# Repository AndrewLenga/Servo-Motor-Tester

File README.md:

# Servo-Motor-Tester
This repository contains the full design suite—including Schematic, PCB Layout, and 3D CAD models—for a high-stability Servo Motor Tester. Engineered using a modified astable multivibrator topology, this device provides a robust hardware solution for validating RC servo response without the need for a microcontroller.
1. Executive Summary
Standard RC servos operate on a specific Pulse Width Modulation (PWM) protocol, requiring a carrier frequency (period) with a high-state duration.
This design leverages the NE555P precision timer to synthesize this waveform by decoupling the charge and discharge timing constants, ensuring high-fidelity signal reproduction for professional benchtop testing.
3. Circuit Architecture & Signal Integrity
A. Non-Symmetric Astable Topology
In a textbook 555 astable configuration, the duty cycle is constrained to achieve the duty cycle required for servo control, this design incorporates a signal diode in parallel with the discharge path.
Charging Phase: The timing capacitor charges through the series combination of the potentiometer 

Discharging Phase: 
It provides a low-impedance return path to Pin 7 (Discharge), effectively bypassing the primary timing resistors.

Implementation Specifications
Parameter	Specification
Logic Family	Bipolar NE555 / CMOS Equivalent
Input Voltage ( DC (Regulated)
Operating Frequency	
(Targeted for standard RC protocols)
Output Pulse Range  (Min) to  (Max)
Connector Interface	3-Pin Header (Signal-VCC-GND)
4. Documentation & Manufacturing
This project includes a comprehensive set of production files:
Schematic: Hierarchical design focusing on signal flow and net-clearance.

PCB Layout: Optimized for a compact footprint with enhanced ground planes for EMI reduction.

3D Model: STEP/STL files for mechanical integration and enclosure design.

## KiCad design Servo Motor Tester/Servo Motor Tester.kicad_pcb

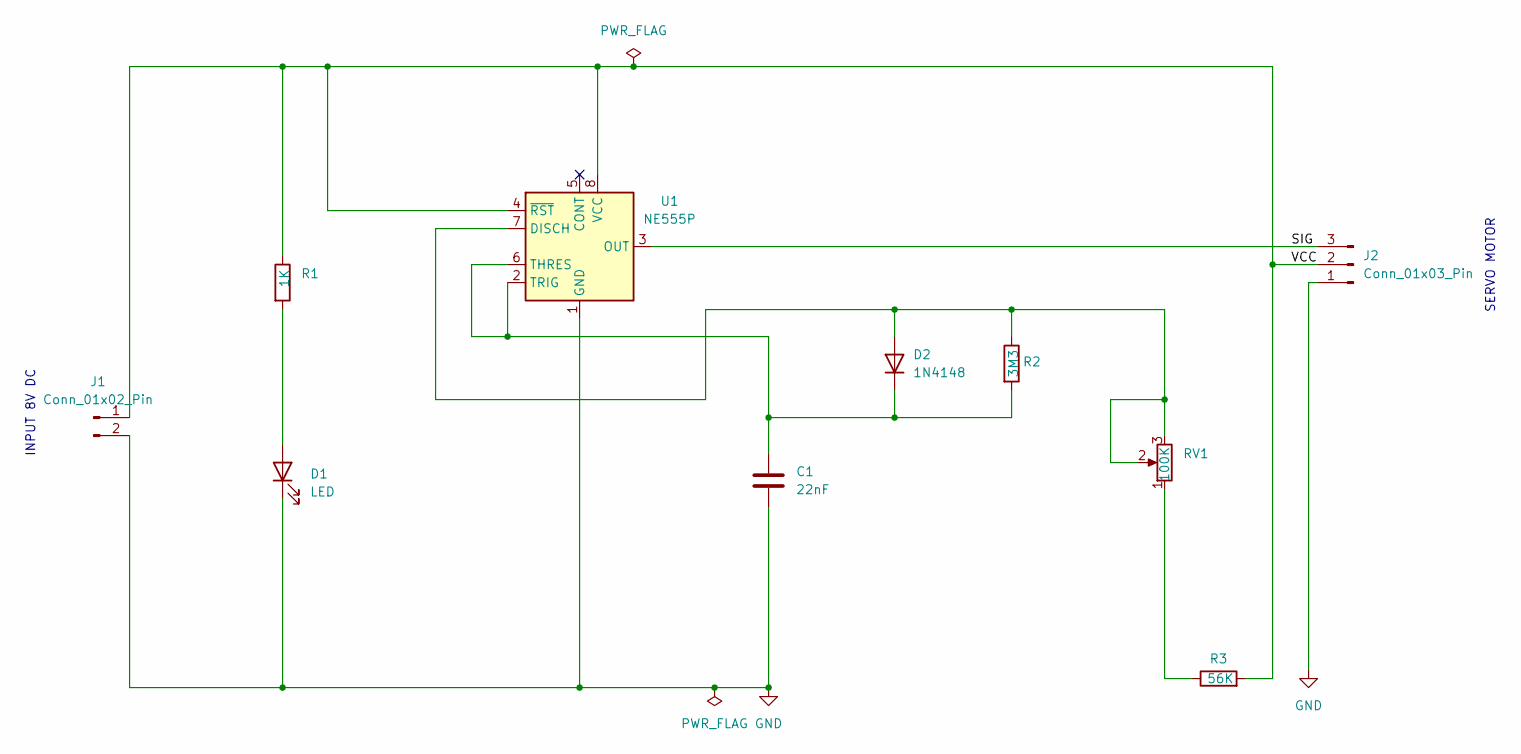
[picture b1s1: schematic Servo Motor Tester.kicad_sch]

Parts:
C1: 22nF; C_Disc_D4.3mm_W1.9mm_P5.00mm
D1: LED; LED_D3.0mm
D2: 1N4148; D_DO-35_SOD27_P7.62mm_Horizontal
J1: Conn_01x02_Pin; PinHeader_1x02_P2.54mm_Horizontal
J2: Conn_01x03_Pin; PinHeader_1x03_P2.54mm_Horizontal
R1: 1K; R_Axial_DIN0204_L3.6mm_D1.6mm_P7.62mm_Horizontal
R2: 3M3; R_Axial_DIN0207_L6.3mm_D2.5mm_P7.62mm_Horizontal
R3: 56K; R_Axial_DIN0207_L6.3mm_D2.5mm_P7.62mm_Horizontal
RV1: 100K; Potentiometer_Alps_RK163_Single_Horizontal
U1: NE555P; DIP-8_W7.62mm

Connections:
/SIG: J2.3, U1.3 (OUT)
/VCC: J1.1, J2.2, R1.1, R3.2, U1.4 (~RST), U1.8 (VCC)
GND: C1.2, D1.1 (K), J1.2, J2.1, U1.1 (GND)
unnamed: D1.2 (A), R1.2
unnamed: D2.2 (A), R2.1, RV1.2, RV1.3, U1.7 (DISCH)
unnamed: C1.1, D2.1 (K), R2.2, U1.2 (TRIG), U1.6 (THRES)
unnamed: R3.1, RV1.1

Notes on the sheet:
SERVO MOTOR
INPUT 8V DC

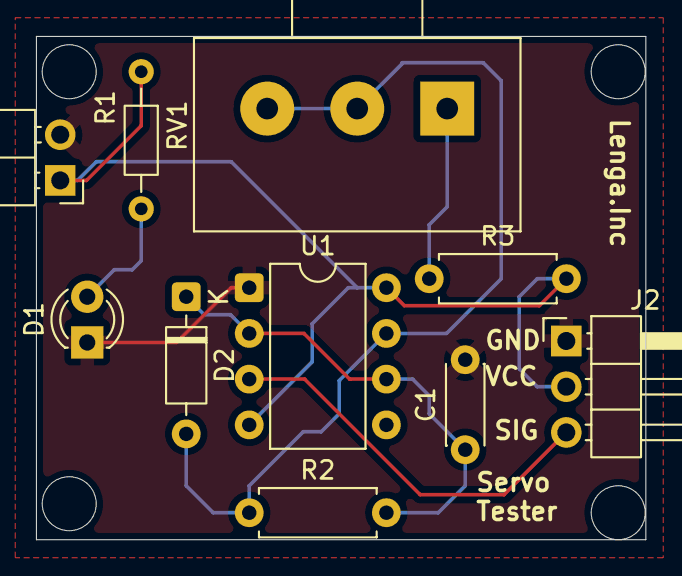
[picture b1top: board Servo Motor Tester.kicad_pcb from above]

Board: 2 copper layers, 33.9 x 28.0 mm, 10 parts (0 on the bottom side), 7 nets.
